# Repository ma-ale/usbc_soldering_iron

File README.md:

# USB-C Soldering Iron

Repo for a cool usb-c soldering iron that uses C245 cartridges and power up to 130W.

Read the [project report](doc/report/README.md) (in italian).

# IDEAS

* USB-C connector on the edge of the PCB like the [alientek T90B](https://youtu.be/Xl0IKpvlF3Y?si=ecKIGLwI0vSPZbJ4&t=7) (clamping plate)
* OLED Screen on a separate PCB, same project with a V-Cut
* More compact tip recess, stabilized by a, aluminium ring, maybe bought at the hardware store
* Single screw disassembly
* 13mm grip dimensions and 18mm otherwise
* 1mm walls in PETG
* Add a ~small~ button to the bootsel line

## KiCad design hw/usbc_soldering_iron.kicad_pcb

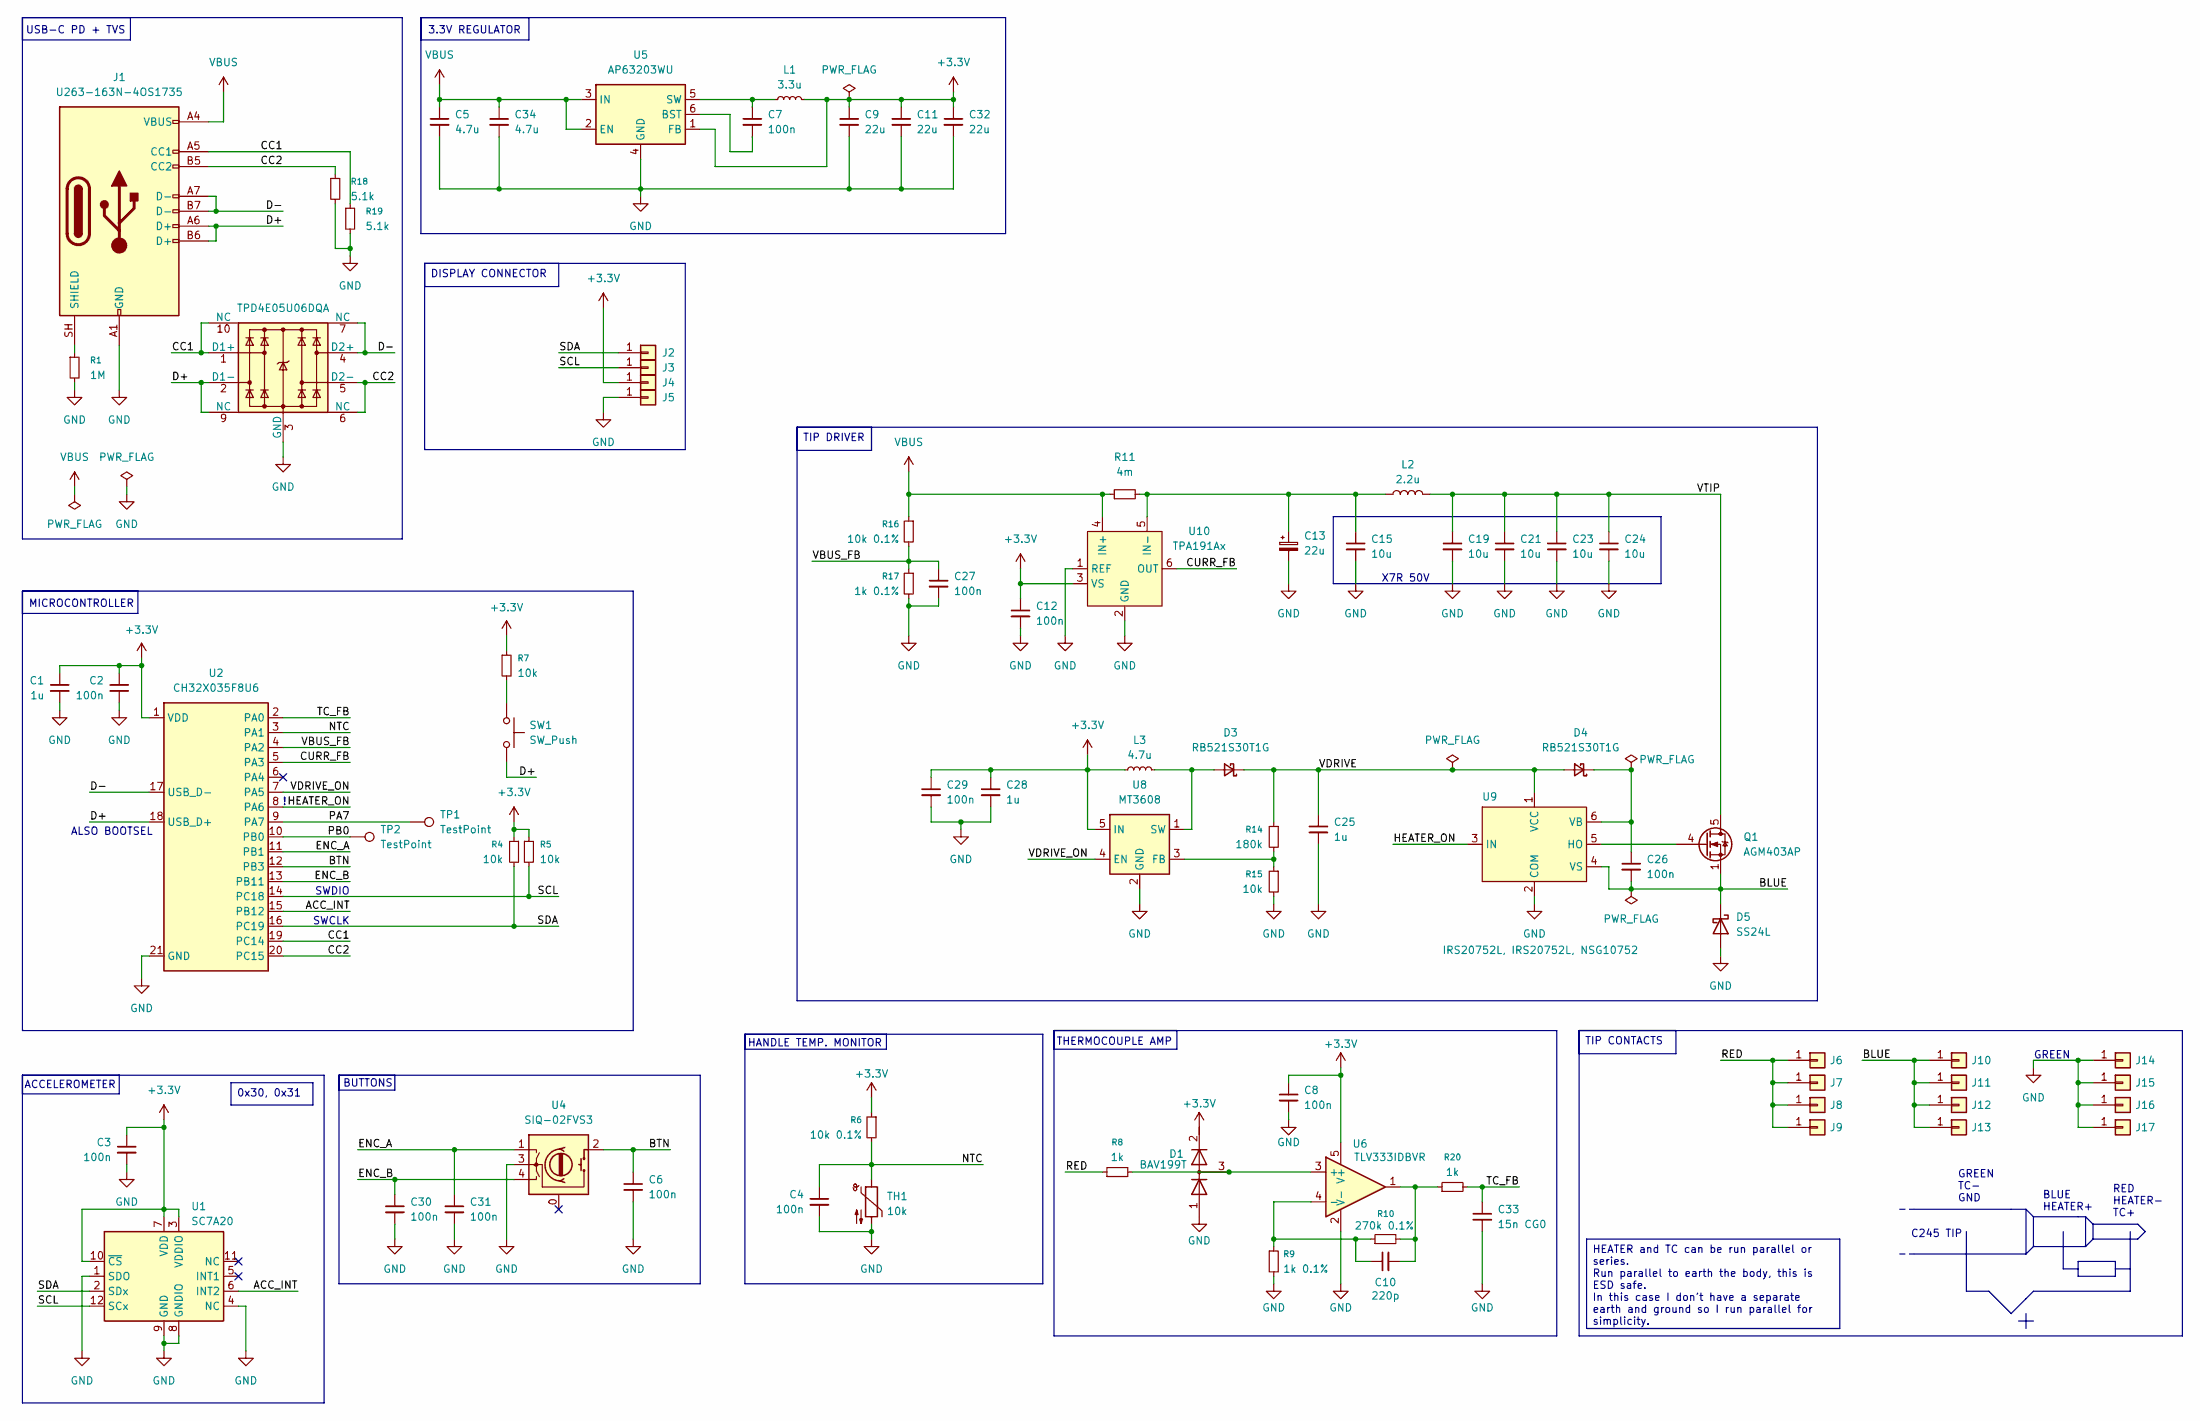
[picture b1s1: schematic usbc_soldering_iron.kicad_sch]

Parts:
C1, C25, C28: 1u; C_0603_1608Metric
C2, C3, C4, C6, C7, C8, C12, C26, C27, C29, C30, C31: 100n; C_0603_1608Metric
C5, C34: 4.7u; C_0805_2012Metric
C9, C11, C32: 22u; C_0603_1608Metric
C10: 220p; C_0603_1608Metric
C13: 22u; CP-SMD_L7.3-W4.3-FD
C15, C19, C21, C23, C24: 10u; C_1210_3225Metric
C33: 15n CG0; C_0603_1608Metric
D1: BAV199T; SOT-523
D3, D4: RB521S30T1G; D_SOD-523
D5: SS24L; D_SOD-123F
J1: U263-163N-4OS1735; USB-SMD_HC-TYPE-C-24P-CP1.0-5A-L10.45-01
J2, J3, J4, J5: Conn_01x01; SolderWirePad_1x01_SMD_1x2mm
J6, J7, J8, J9, J10, J11, J12, J13, J14, J15, J16, J17: Conn_01x01; SolderWire-1sqmm_1x01_D1.4mm_OD2.7mm
L1: 3.3u; L_Changjiang_FTC201612S_Handsolder
L2: 2.2u; L_Changjiang_FNR4030S_Handsolder
L3: 4.7u; L_0603_1608Metric
Q1: AGM403AP; VSON-8_3.3x3.3mm_P0.65mm_NexFET
R1: 1M; R_0603_1608Metric
R4, R5, R7, R15: 10k; R_0603_1608Metric
R6, R16: 10k 0.1%; R_0603_1608Metric
R8, R20: 1k; R_0603_1608Metric
R9, R17: 1k 0.1%; R_0603_1608Metric
R10: 270k 0.1%; R_0603_1608Metric
R11: 4m; R_1206_3216Metric
R14: 180k; R_0603_1608Metric
R18, R19: 5.1k; R_0603_1608Metric
SW1: SW_Push; SW_PUSH_GT-TS201A-H0065
TH1: 10k; R_0603_1608Metric
TP1, TP2: TestPoint; TestPoint_Pad_D1.0mm
U1: SC7A20; LGA-12_2x2mm_P0.5mm
U2: CH32X035F8U6; QFN-20-1EP_3x3mm_P0.4mm_EP1.65x1.65mm; LCSC C42442062
U3: TPD4E05U06DQA; USON-10_2.5x1.0mm_P0.5mm
U4: SIQ-02FVS3; SIQ-02FVS3_Rotary_Encoder
U5: AP63203WU; TSOT-23-6
U6: TLV333IDBVR; SOT-23-5
U8: MT3608; SOT-23-6
U9: IRS20752L, IRS20752L, NSG10752; SOT-23-6
U10: TPA191Ax; SOT-363_SC-70-6

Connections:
+3.3V: C1.1, C2.1, C3.1, C8.1, C9.1, C11.1, C12.1, C28.1, C29.1, C32.1, D1.2 (K), J4.1 (Pin_1_1), L1.2, L3.1, R4.1, R5.1, R6.1, R7.1, U1.3 (VDDIO), U1.7 (VDD), U1.10 (~CS), U2.1 (VDD), U5.1 (FB), U6.5 (V+), U8.5 (IN), U10.3 (VS)
/ACC_INT: U1.6 (INT2), U2.15 (PB12)
/BLUE: C26.2, D5.1 (K), J10.1 (Pin_1_1), J11.1 (Pin_1_1), J12.1 (Pin_1_1), J13.1 (Pin_1_1), Q1.1 (S), Q1.2 (S), Q1.3 (S), U9.4 (VS)
/BTN: C6.1, U2.12 (PB3), U4.2
/CC1: J1.A5 (CC1), R19.1, U2.19 (PC14), U3.1 (D1+), U3.10 (NC)
/CC2: J1.B5 (CC2), R18.1, U2.20 (PC15), U3.5 (D2-), U3.6 (NC)
/CURR_FB: U2.5 (PA3), U10.6 (OUT)
/D+: J1.A6 (D+), J1.B6 (D+), SW1.2, U2.18 (USB_D+), U3.2 (D1-), U3.9 (NC)
/D-: J1.A7 (D-), J1.B7 (D-), U2.17 (USB_D-), U3.4 (D2+), U3.7 (NC)
/ENC_A: C31.1, U2.11 (PB1), U4.1
/ENC_B: C30.1, U2.13 (PB11), U4.4
/HEATER_ON: U2.8 (PA6), U9.3 (IN)
/NTC: C4.1, R6.2, TH1.1, U2.3 (PA1)
/PA7: TP1.1 (1_1), U2.9 (PA7)
/PB0: TP2.1 (1_1), U2.10 (PB0)
/RED: J6.1 (Pin_1_1), J7.1 (Pin_1_1), J8.1 (Pin_1_1), J9.1 (Pin_1_1), R8.1
/SCL: J3.1 (Pin_1_1), R5.2, U1.12 (SCx), U2.14 (PC18)
/SDA: J2.1 (Pin_1_1), R4.2, U1.2 (SDx), U2.16 (PC19)
/TC_FB: C33.1, R20.2, U2.2 (PA0)
/VBUS_FB: C27.1, R16.2, R17.1, U2.4 (PA2)
/VDRIVE: C25.1, D3.1 (K), D4.2 (A), R14.1, U9.1 (VCC)
/VDRIVE_ON: U2.7 (PA5), U8.4 (EN)
/VTIP: C19.1, C21.1, C23.1, C24.1, L2.2, Q1.5 (D)
GND: C1.2, C2.2, C3.2, C4.2, C5.2, C6.2, C8.2, C9.2, C11.2, C12.2, C13.2, C15.2, C19.2, C21.2, C23.2, C24.2, C25.2, C27.2, C28.2, C29.2, C30.2, C31.2, C32.2, C33.2, C34.2, D1.1 (A), D5.2 (A), J1.A1 (GND), J1.A12 (GND), J1.B1 (GND), J1.B12 (GND), J5.1 (Pin_1_1), J14.1 (Pin_1_1), J15.1 (Pin_1_1), J16.1 (Pin_1_1), J17.1 (Pin_1_1), R1.2, R9.2, R15.2, R17.2, R18.2, R19.2, TH1.2, U1.1 (SDO), U1.4 (NC), U1.8 (GNDIO), U1.9 (GND), U2.21 (GND), U3.3 (GND), U3.8 (GND), U4.3, U5.4 (GND), U6.2 (V-), U8.2 (GND), U9.2 (COM), U10.1 (REF), U10.2 (GND)
unnamed: C10.2, R10.2, R20.1, U6.1
unnamed: D1.3 (common), R8.2, U6.3 (+)
unnamed: D3.2 (A), L3.2, U8.1 (SW)
unnamed: C26.1, D4.1 (K), U9.6 (VB)
unnamed: J1.SH (SHIELD), R1.1
unnamed: Q1.4 (G), U9.5 (HO)
unnamed: R7.2, SW1.1
unnamed: C7.2, U5.6 (BST)
unnamed: C7.1, L1.1, U5.5 (SW)
unnamed: C10.1, R9.1, R10.1, U6.4 (-)
unnamed: R14.2, R15.1, U8.3 (FB)
unnamed: C13.1, C15.1, L2.1, R11.2, U10.5 (IN-)
VBUS: C5.1, C34.1, J1.A4 (VBUS), J1.A9 (VBUS), J1.B4 (VBUS), J1.B9 (VBUS), R11.1, R16.1, U5.2 (EN), U5.3 (IN), U10.4 (IN+)

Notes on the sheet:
SWCLK
RED HEATER- TC+
3.3V REGULATOR
SWDIO
ALSO BOOTSEL
USB-C PD + TVS
BUTTONS
ACCELEROMETER
BLUE HEATER+
HANDLE TEMP. MONITOR
GREEN
X7R 50V
THERMOCOUPLE AMP
MICROCONTROLLER
C245 TIP
GREEN TC- GND
TIP DRIVER
0x30, 0x31
DISPLAY CONNECTOR
HEATER and TC can be run parallel or series. Run parallel to earth the body, this is ESD safe. In this case I don't have a separate earth and ground so I run parallel for simplicity.
TIP CONTACTS

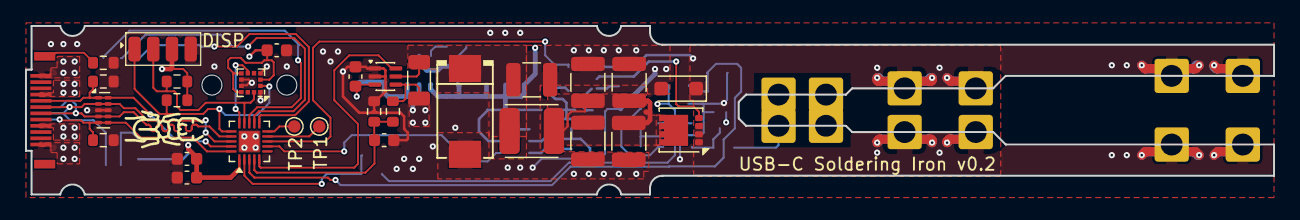
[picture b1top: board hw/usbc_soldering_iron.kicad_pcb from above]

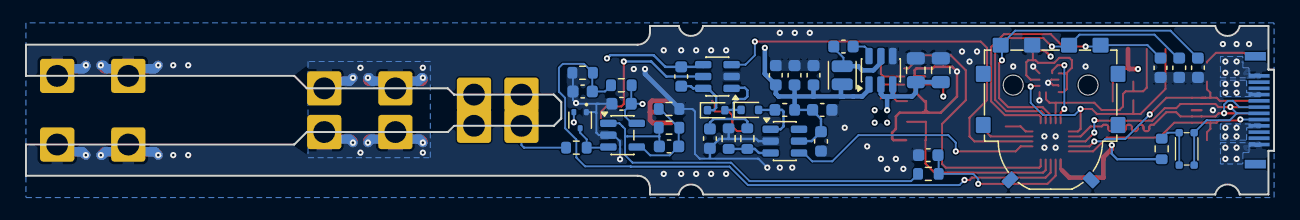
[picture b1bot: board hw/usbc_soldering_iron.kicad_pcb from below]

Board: 4 copper layers, 100.0 x 13.5 mm, 82 parts (37 on the bottom side), 37 nets.

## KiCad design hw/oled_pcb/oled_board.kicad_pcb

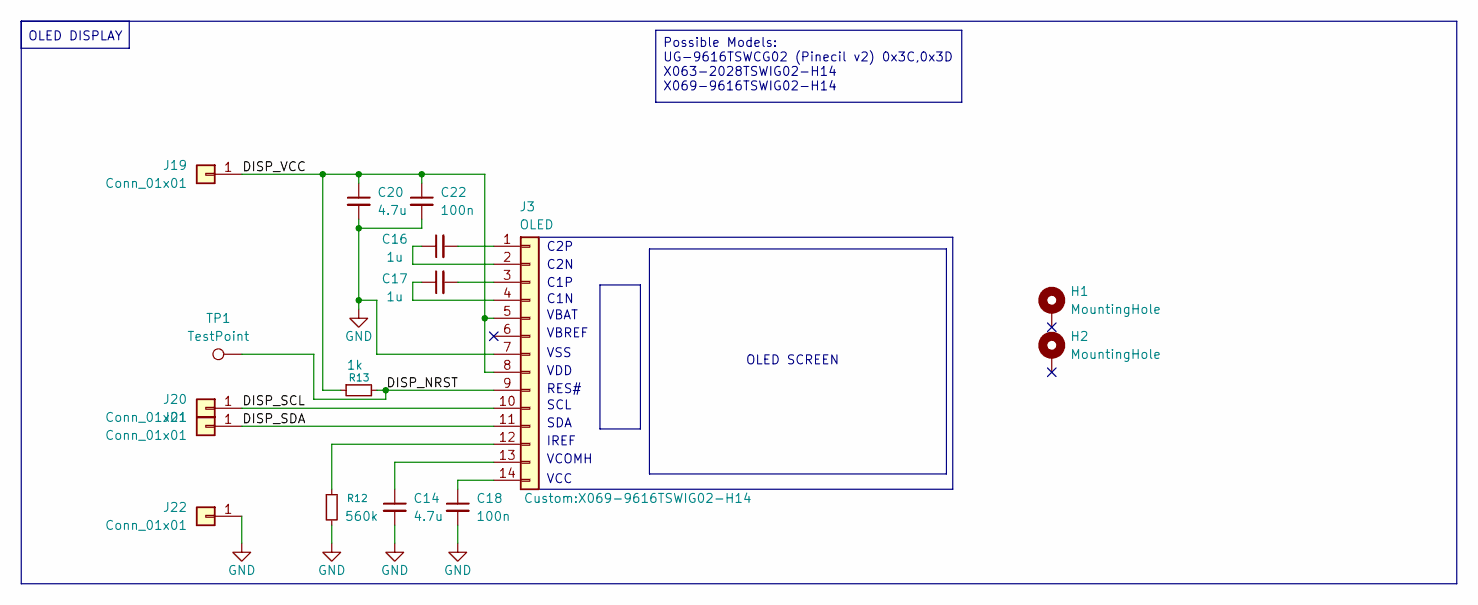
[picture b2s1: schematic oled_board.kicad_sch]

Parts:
C14, C20: 4.7u; C_0603_1608Metric
C16, C17: 1u; C_0603_1608Metric
C18, C22: 100n; C_0603_1608Metric
H1, H2: MountingHole; Mounting_Wuerth_WA-SMSI-M2_H0.5mm_9774005243
J3: OLED; X069-9616TSWIG02-H14
J19, J20, J21, J22: Conn_01x01; SolderWirePad_1x01_SMD_1x2mm
R12: 560k; R_0603_1608Metric
R13: 1k; R_0603_1608Metric
TP1: TestPoint; TestPoint_Pad_D1.0mm

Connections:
/DISP_NRST: J3.9, R13.2, TP1.1 (1_1)
/DISP_SCL: J3.10, J20.1 (Pin_1_1)
/DISP_SDA: J3.11, J21.1 (Pin_1_1)
/DISP_VCC: C20.1, C22.1, J3.5, J3.8, J19.1 (Pin_1_1), R13.1
GND: C14.2, C18.2, C20.2, C22.2, J3.7, J22.1 (Pin_1_1), R12.2
unnamed: C16.2, J3.1
unnamed: C16.1, J3.2
unnamed: C17.2, J3.3
unnamed: C17.1, J3.4
unnamed: J3.12, R12.1
unnamed: C14.1, J3.13
unnamed: C18.1, J3.14

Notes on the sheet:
C2N
SCL
RES#
C1P
IREF
C1N
C2P
VDD
OLED SCREEN
VCC
SDA
VBREF
OLED DISPLAY
VBAT
VSS
VCOMH
Possible Models: UG-9616TSWCG02 (Pinecil v2) 0x3C,0x3D X063-2028TSWIG02-H14 X069-9616TSWIG02-H14

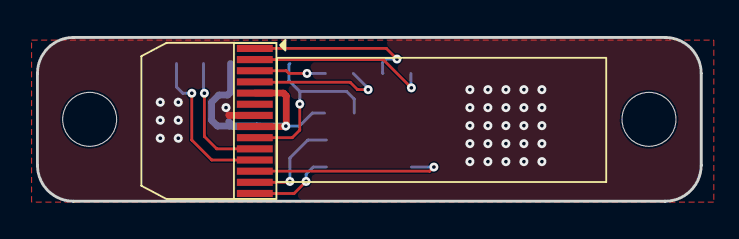
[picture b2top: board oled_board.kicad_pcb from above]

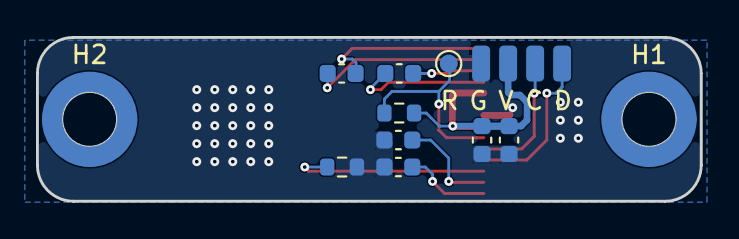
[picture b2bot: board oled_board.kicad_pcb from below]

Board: 2 copper layers, 36.9 x 9.1 mm, 16 parts (15 on the bottom side), 12 nets.

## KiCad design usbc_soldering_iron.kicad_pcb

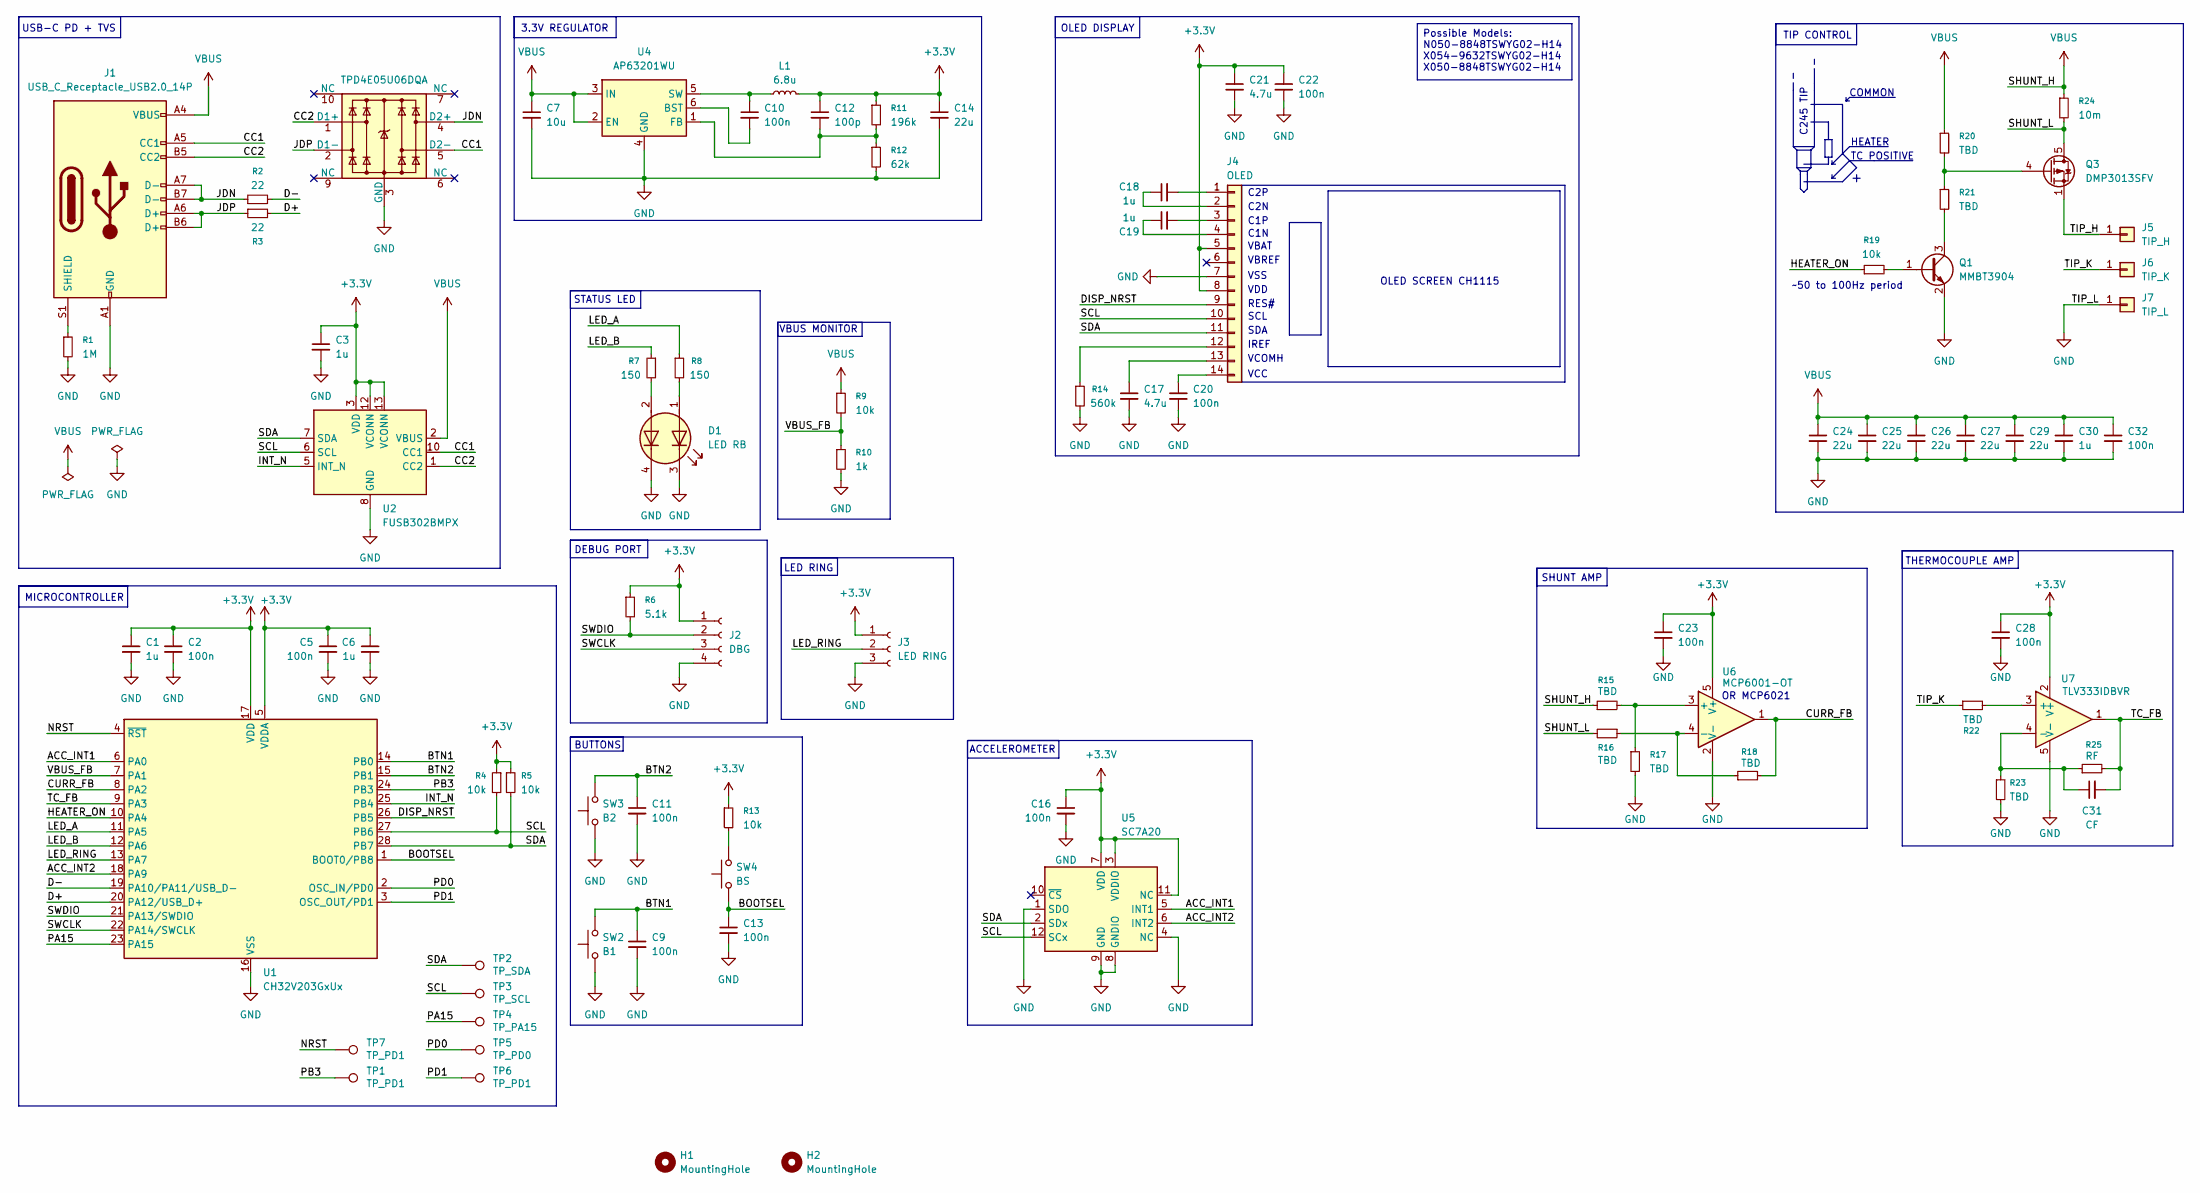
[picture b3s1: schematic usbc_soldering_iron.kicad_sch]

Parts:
C1, C3, C6, C18, C19: 1u; C_0603_1608Metric
C2, C5, C9, C10, C11, C13, C16, C20, C22, C23, C28, C32: 100n; C_0603_1608Metric
C7: 10u; C_0805_2012Metric
C12: 100p; C_0603_1608Metric
C14, C24, C25, C26, C27, C29: 22u; C_0805_2012Metric
C17, C21: 4.7u; C_0603_1608Metric
C30: 1u; C_0805_2012Metric
C31: CF; C_0603_1608Metric
D1: LED RB; LED_Avago_PLCC4_3.2x2.8mm_CW
H1, H2: MountingHole; MountingHole_2.2mm_M2
J1: USB_C_Receptacle_USB2.0_14P; USB_C_Receptacle_G-Switch_GT-USB-7025
J2: DBG
J3: LED RING
J4: OLED; FPC_14
J5: TIP_H
J6: TIP_K
J7: TIP_L
L1: 6.8u; L_Changjiang_FTC201607S
Q1: MMBT3904; SOT-23
Q3: DMP3013SFV; Diodes_PowerDI3333-8
R1: 1M; R_0603_1608Metric
R2, R3: 22; R_0603_1608Metric
R4, R5, R9, R13, R19: 10k; R_0603_1608Metric
R6: 5.1k; R_0603_1608Metric
R7, R8: 150; R_0603_1608Metric
R10: 1k; R_0603_1608Metric
R11: 196k; R_0603_1608Metric
R12: 62k; R_0603_1608Metric
R14: 560k; R_0603_1608Metric
R15, R16, R17, R18, R20, R21, R22, R23: TBD; R_0603_1608Metric
R24: 10m; R_1206_3216Metric
R25: RF; R_0603_1608Metric
SW2: B1; SW_SPST_TS-1088-xR020
SW3: B2; SW_SPST_TS-1088-xR020
SW4: BS; SW_SPST_TS-1088-xR020
TP1, TP6, TP7: TP_PD1; TestPoint_Pad_D1.0mm
TP2: TP_SDA; TestPoint_Pad_D1.0mm
TP3: TP_SCL; TestPoint_Pad_D1.0mm
TP4: TP_PA15; TestPoint_Pad_D1.0mm
TP5: TP_PD0; TestPoint_Pad_D1.0mm
U1: CH32V203GxUx; WQFN-28-1EP_4x4mm_P0.4mm_EP2.7x2.7mm
U2: FUSB302BMPX; WQFN-14-1EP_2.5x2.5mm_P0.5mm_EP1.45x1.45mm
U4: AP63201WU; TSOT-23-6
U5: SC7A20; LGA-12_2x2mm_P0.5mm
U6: MCP6001-OT; SOT-23-5
U7: TLV333IDBVR; SOT-23-5
U8: TPD4E05U06DQA; USON-10_2.5x1.0mm_P0.5mm

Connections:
+3.3V: C1.1, C2.1, C3.1, C5.1, C6.1, C12.1, C14.1, C16.1, C21.1, C22.1, C23.1, C28.1, J2.1, J3.1, J4.5, J4.8, L1.2, R4.1, R5.1, R6.1, R11.1, R13.1, U1.5 (VDDA), U1.17 (VDD), U2.3 (VDD), U2.4 (VDD), U2.12 (VCONN), U2.13 (VCONN), U5.3 (VDDIO), U5.7 (VDD), U5.11 (NC), U6.5 (V+), U7.2 (V+)
/ACC_INT1: U1.6 (PA0), U5.5 (INT1)
/ACC_INT2: U1.18 (PA9), U5.6 (INT2)
/BOOTSEL: C13.1, SW4.1, U1.1 (BOOT0/PB8)
/BTN1: C9.1, SW2.2, U1.14 (PB0)
/BTN2: C11.1, SW3.2, U1.15 (PB1)
/CC1: J1.A5 (CC1), U2.10 (CC1), U2.11 (CC1), U8.5 (D2-)
/CC2: J1.B5 (CC2), U2.1 (CC2), U2.14 (CC2), U8.1 (D1+)
/CURR_FB: R18.2, U1.8 (PA2), U6.1
/D+: R3.2, U1.20 (PA12/USB_D+)
/D-: R2.2, U1.19 (PA10/PA11/USB_D-)
/DISP_NRST: J4.9, U1.26 (PB5)
/HEATER_ON: R19.1, U1.10 (PA4)
/INT_N: U1.25 (PB4), U2.5 (INT_N)
/JDN: J1.A7 (D-), J1.B7 (D-), R2.1, U8.4 (D2+)
/JDP: J1.A6 (D+), J1.B6 (D+), R3.1, U8.2 (D1-)
/LED_A: R8.1, U1.11 (PA5)
/LED_B: R7.1, U1.12 (PA6)
/LED_RING: J3.2, U1.13 (PA7)
/NRST: TP7.1, U1.4 (~RST)
/PA15: TP4.1, U1.23 (PA15)
/PB3: TP1.1, U1.24 (PB3)
/PD0: TP5.1, U1.2 (OSC_IN/PD0)
/PD1: TP6.1, U1.3 (OSC_OUT/PD1)
/SCL: J4.10, R4.2, TP3.1, U1.27 (PB6), U2.6 (SCL), U5.12 (SCx)
/SDA: J4.11, R5.2, TP2.1, U1.28 (PB7), U2.7 (SDA), U5.2 (SDx)
/SHUNT_L: Q3.5 (D), R16.2, R24.2
/SWCLK: J2.3, U1.22 (PA14/SWCLK)
/SWDIO: J2.2, R6.2, U1.21 (PA13/SWDIO)
/TC_FB: C31.2, R25.2, U1.9 (PA3), U7.1
/TIP_H: J5.1, Q3.1 (S), Q3.2 (S), Q3.3 (S)
/TIP_K: J6.1, R22.1
/VBUS_FB: R9.2, R10.1, U1.7 (PA1)
GND: C1.2, C2.2, C3.2, C5.2, C6.2, C7.2, C9.2, C11.2, C13.2, C14.2, C16.2, C17.2, C20.2, C21.2, C22.2, C23.2, C24.2, C25.2, C26.2, C27.2, C28.2, C29.2, C30.2, C32.2, D1.3 (K1), D1.4 (K2), J1.A1 (GND), J1.A12 (GND), J1.B1 (GND), J1.B12 (GND), J2.4, J3.3, J4.7, J7.1, Q1.2 (E), R1.2, R10.2, R12.2, R14.2, R17.2, R23.2, SW2.1, SW3.1, U1.16 (VSS), U1.29 (VSS), U2.8 (GND), U2.9 (GND), U2.15 (GND), U4.4 (GND), U5.1 (SDO), U5.4 (NC), U5.8 (GNDIO), U5.9 (GND), U6.2 (V-), U7.5 (V-), U8.3 (GND), U8.8 (GND)
unnamed: D1.1 (A1), R8.2
unnamed: D1.2 (A2), R7.2
unnamed: J1.S1 (SHIELD), R1.1
unnamed: C18.2, J4.1
unnamed: C18.1, J4.2
unnamed: C19.2, J4.3
unnamed: C19.1, J4.4
unnamed: J4.12, R14.1
unnamed: C17.1, J4.13
unnamed: C20.1, J4.14
unnamed: Q1.1 (B), R19.2
unnamed: Q1.3 (C), R21.2
unnamed: Q3.4 (G), R20.2, R21.1
unnamed: R13.2, SW4.2
unnamed: C10.2, U4.6 (BST)
unnamed: C12.2, R11.2, R12.1, U4.1 (FB)
unnamed: C10.1, L1.1, U4.5 (SW)
unnamed: R15.2, R17.1, U6.3 (+)
unnamed: R16.1, R18.1, U6.4 (-)
unnamed: R22.2, U7.3 (+)
unnamed: C31.1, R23.1, R25.1, U7.4 (-)
VBUS: C7.1, C24.1, C25.1, C26.1, C27.1, C29.1, C30.1, C32.1, J1.A4 (VBUS), J1.A9 (VBUS), J1.B4 (VBUS), J1.B9 (VBUS), R9.1, R15.1, R20.1, R24.1, U2.2 (VBUS), U4.2 (EN), U4.3 (IN)

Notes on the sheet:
COMMON
~50 to 100Hz period
3.3V REGULATOR
C2N
OR MCP6021
USB-C PD + TVS
BUTTONS
DEBUG PORT
SCL
RES#
C1P
ACCELEROMETER
HEATER
IREF
C1N
C2P
VDD
TC POSITIVE
OLED SCREEN CH1115
VCC
TIP CONTROL
SDA
VBREF
SHUNT AMP
STATUS LED
OLED DISPLAY
VBAT
VSS
VCOMH
THERMOCOUPLE AMP
C245 TIP
LED RING
MICROCONTROLLER
VBUS MONITOR
Possible Models: N050-8848TSWYG02-H14 X054-9632TSWYG02-H14 X050-8848TSWYG02-H14

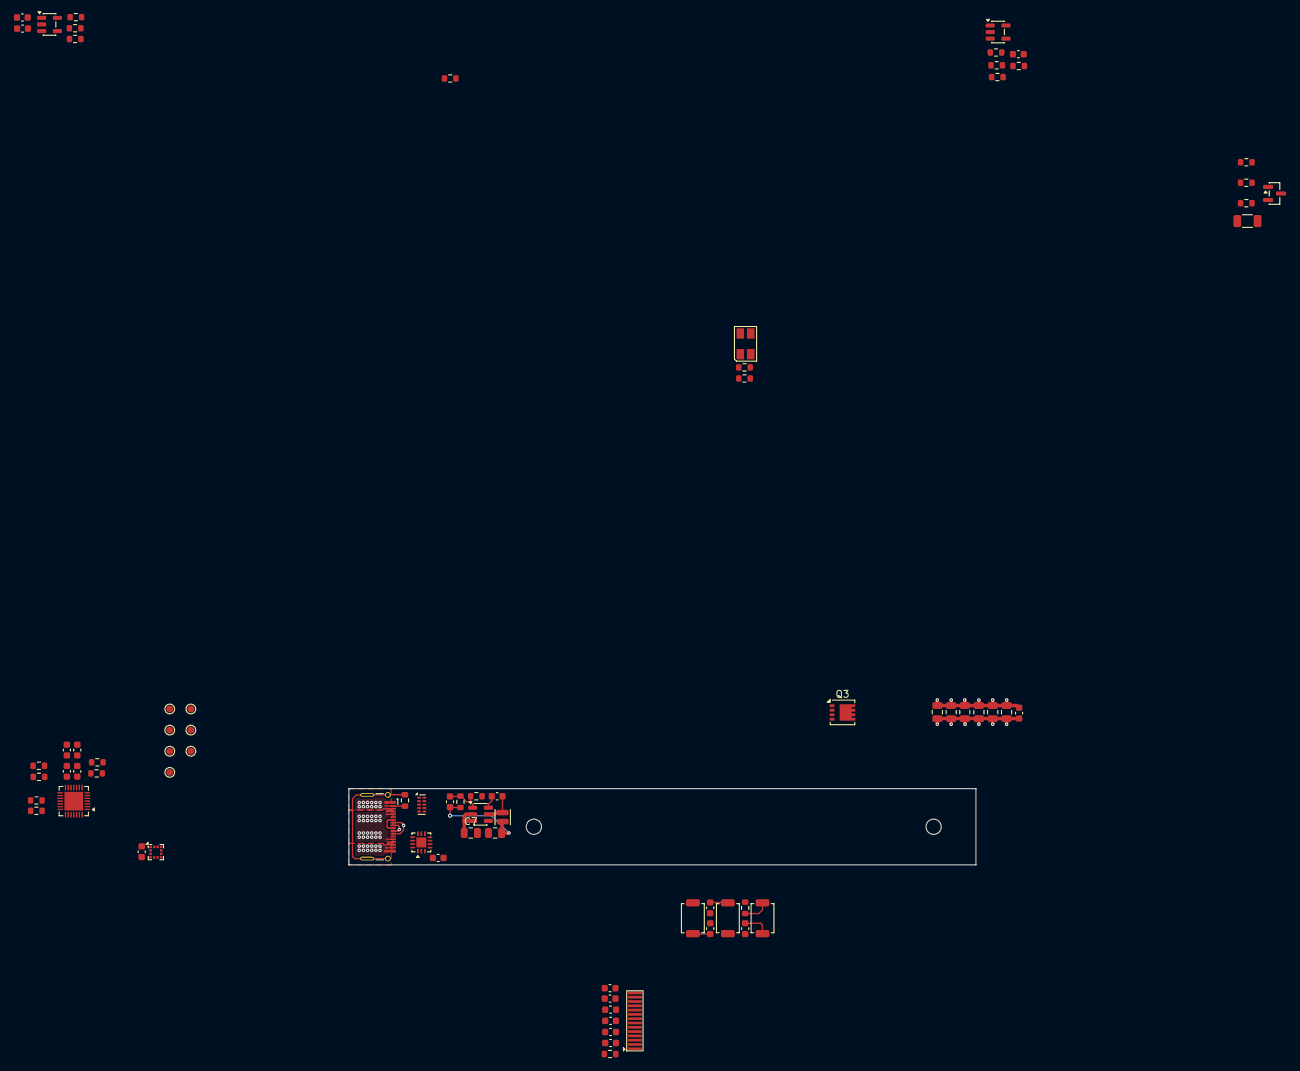
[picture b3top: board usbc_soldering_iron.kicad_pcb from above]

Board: 4 copper layers, 90.5 x 11.0 mm, 79 parts (0 on the bottom side), 53 nets.

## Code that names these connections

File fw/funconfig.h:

#ifndef _FUNCONFIG_H
#define _FUNCONFIG_H

#define FUNCONF_USE_DEBUGPRINTF 0 // can only have one printf
#define FUNCONF_USE_USBPRINTF   1
#define FUNCONF_DEBUG_HARDFAULT 0
#define CH32X035                1
#define I2C_TARGET              I2C1
#define FRAME_TIME_MS           20 // 50Hz
#define PWM_FREQ_HZ             100000 // TIM3 PWM frequency

// Pin definitions
#define PIN_VBUS     PA0  // vbus voltage feedback
#define PIN_CURRENT  PA1  // current feedback
#define PIN_NTC      PA2  // ntc temperature sensor
#define PIN_TEMP     PA3  // thermocouple amplifier
#define PIN_12V      PA5  // 12V regulator enable
#define PIN_HEATER   PA6  // power mosfet gate control
#define PIN_ENC_A    PB3  // rotary encoder A
#define PIN_ENC_B    PB11 // rotary encoder B
#define PIN_BTN      PB1  // rotary encoder button

// Analog channel definitions
#define VBUS_ADC_CHANNEL    ANALOG_0 // PA0
#define CURRENT_ADC_CHANNEL ANALOG_1 // PA1
#define NTC_ADC_CHANNEL     ANALOG_2 // PA2
#define TEMP_ADC_CHANNEL    ANALOG_3 // PA3
#define VREF_INT_CHANNEL    15       // Internal channel set to 1.2V reference

#define ENCODER_INV true
#define ENCODER_FAST 3

#define MAX_BOARD_TEMP 50
#define MAX_TIP_TEMP   500
#define TURN_OFF_DELAY 3
#define CYCLES_PER_MEASURE 2
#define BOARD_MAX_VOLTAGE 28000
#define MIN_TIP_SET_TEMP 100
#define MAX_TIP_SET_TEMP 420



#endif // _FUNCONFIG_H

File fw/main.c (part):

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	btn->now = state;
}

#define button_rising(btn) ((btn).now == true && (btn).prev == false)
#define button_falling(btn) ((btn).now == false && (btn).prev == true)


/* ------------------------------ Global State ------------------------------ */
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
	// FIXME: even with interrupts disabled and debounce, a single detent triggers
	// multiple interrupts, leading to multiple encoder updates in a short time.
	if (funDigitalRead(PIN_BTN) == 0) return;
	bool a = funDigitalRead(PIN_ENC_A);
	bool b = funDigitalRead(PIN_ENC_B);
	Delay_Us(100);
	if (a != funDigitalRead(PIN_ENC_A) || b != funDigitalRead(PIN_ENC_B))
		return; // debounce

	uint8_t current_state = (a << 1) | b;
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	last_state = current_state;
}

// Attached to PIN_ENC_A rising and falling edges
void EXTI7_0_IRQHandler(void) __attribute__((interrupt));
void EXTI7_0_IRQHandler(void)
{
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	__enable_irq();
}

// Attached to PIN_ENC_B rising and falling edges
void EXTI15_8_IRQHandler(void) __attribute__((interrupt));
void EXTI15_8_IRQHandler(void)
{
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	AFIO->PCFR1 &= ~(0b0111 << 24);
	AFIO->PCFR1 |=   0b0100 << 24;

	// Map SCL to PC18 and SDA to PC19
	AFIO->PCFR1 |= 0b0101 << 2;
	// Manually set the I2C pins to Alternate Function IO,  CNF=10b, MODE=10b
	GPIOC->CFGXR &= ~((0xF << 8) | (0xF << 12)); // first clear the bits
	// then set them
	GPIOC->CFGXR |= 0b1010 << 8; // PC18
	GPIOC->CFGXR |= 0b1010 << 12; // PC19
}


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	// (= initiate update) (auto-clears)
	TIM3->CHCTLR1 |= TIM_OC1M_2 | TIM_OC1M_1 | TIM_OC1PE;

	// Enable channel 1 output (PA6)
	TIM3->CCER |= TIM_CC1E | ( TIM_CC1P & TIM3_DEFAULT );

	// CTLR1: default is up, events generated, edge align
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	// ====================== Analog pin configuration ====================== //
	funPinMode(PIN_VBUS, GPIO_CFGLR_IN_ANALOG);
	funPinMode(PIN_CURRENT, GPIO_CFGLR_IN_ANALOG);
	funPinMode(PIN_NTC, GPIO_CFGLR_IN_ANALOG);
	funPinMode(PIN_TEMP, GPIO_CFGLR_IN_ANALOG);

	// Analog inputs setup (dma and injection conversion)
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	funPinMode(PIN_DISP_RST, GPIO_CFGLR_OUT_10Mhz_PP);
	funDigitalWrite(PIN_DISP_RST, 1);

	funPinMode(PIN_ENC_A, GPIO_CFGLR_IN_PUPD); // enable pull-up/down
	funDigitalWrite(PIN_ENC_A, 1);             // specify pull-up
	funPinMode(PIN_ENC_B, GPIO_CFGLR_IN_PUPD); // enable pull-up/down
	funDigitalWrite(PIN_ENC_B, 1);             // specify pull-up
	funPinMode(PIN_BTN, GPIO_CFGLR_IN_FLOAT);

	// Setup PWM timer, includes pin setup
	setup_pwm();
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
	// =========================== Encoder Setup ============================ //
	// Configure the IO as an interrupt.
	// PIN_ENC_B is on port B, channel 11
	AFIO->EXTICR1 |= AFIO_EXTICR1_EXTI11_PB; // Port B channel (pin) 11
	EXTI->INTENR |= EXTI_INTENR_MR11;        // Enable EXT11
	EXTI->FTENR |= EXTI_FTENR_TR11;          // Falling edge trigger
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	// enable interrupt
	NVIC_EnableIRQ(EXTI15_8_IRQn);

	// PIN_ENC_A is on port B, channel 3
	AFIO->EXTICR1 |= AFIO_EXTICR1_EXTI3_PB; // Port B channel (pin) 3
	EXTI->INTENR |= EXTI_INTENR_MR3;        // Enable EXT3
	EXTI->FTENR |= EXTI_FTENR_TR3;          // Falling edge trigger
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static inline void update_tip_and_vcc(void)
{
	// Tip calibration factors
	const fp16_t tip_k = num2fp(0, 14473, 5);
	const fp16_t tip_off = num2fp(0, 0, 0);

	adc_injection_conversion();
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	struct button btn;
	button_init(&btn, true);
	for (;;) {
		button_update(&btn, funDigitalRead(PIN_BTN));

		update_power_and_temperature();

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
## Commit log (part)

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2026-01-16 board dimensions and different components
2026-01-16 some things needed to be 0805
2026-01-20 progress on schematic and ui draft
2026-01-20 mosfet protection and low side current sensing
2026-01-20 removed LED and added NTC
2026-01-22 added tip 3d model
2026-01-22 ui font concept update
2026-01-22 update model to freecad stable version
2026-01-22 added pads for tip connector
2026-01-24 big update
    * drawn contacts
    * done board outline in cad
    * reverted to high-side monitoring with ad-hoc ic
2026-01-24 FIX MOSFET ORIENTATION
2026-02-03 excel dei buck
2026-02-03 stima della massima potenza dissipata
2026-02-07 buck converter
2026-02-07 ltspice simulations
2026-02-10 stuff
2026-02-13 mosfets and driver
2026-02-14 more realistic pi filter
2026-02-14 different mosfets
2026-02-17 complete model test
2026-02-18 work on model
2026-02-18 rotary encoder and model for usb receptacle
2026-02-18 started work on report
2026-02-19 smile for the camera
2026-02-19 changed power stage and monitoring ICs
2026-02-19 added README
2026-02-19 more work on report
2026-02-20 simulate the gate driver IC
2026-02-20 report: work on mosfet and driver
2026-02-22 separate boost for gate driver
2026-02-22 removed i2c temp sensor and high side bus switch
2026-02-22 preliminary BOM and schematic
2026-02-22 fixed buck, same family
2026-02-24 revised schematic
    - changed mcu to ch32x035
    - removed fusbxx pd controller, since it's integrated into the mcu
    - reverted the ina226 to the tpa191
    - removed temperature sensor in favor of an ntc
    - routed tip contacts correctly
2026-02-24 bom for revised schematic
2026-02-24 changed usb-c connector
2026-02-25 simulazioni con derating per dc bias
2026-02-25 link sul derating
2026-02-25 flyback diode to the tip
2026-02-25 list of good mosfets
2026-02-26 removed the diocane filter in favor of capacitors
2026-02-28 different capacitors in sim with pi filter
2026-02-28 trying new capacitors
2026-02-28 samsung mlccs
2026-02-28 Revert "samsung mlccs"
    This reverts commit f0811c47dd4636ecc8ad168b69960cac51ca3142.
2026-02-28 Revert "trying new capacitors"
    This reverts commit 6cb91291f39b019d0baab4303cfee70c88c38332.
2026-02-28 Revert "different capacitors in sim with pi filter"
    This reverts commit 30c0aa5cba112ce18ca016d04ddbcca1eab52d60.
2026-02-28 different smaller capacitor
2026-02-28 different capacitors and new bom
2026-03-01 ceramic capacitor
2026-03-02 new filter design, may work lmao
2026-03-05 some component changes
2026-03-06 boxed version
2026-03-07 test pads
2026-03-08 finished pcb
2026-03-09 switch-off simulations and in-stock capacitors
2026-03-10 silkscreen
2026-03-10 different current sensor
2026-03-11 minor tweaks
2026-03-11 lcsc order bom
2026-03-21 3D model of first enclosure
2026-03-25 firmware setup
2026-03-25 test new outline
2026-03-25 some todos
2026-03-25 updated to kicad 10.0
2026-04-04 first (non working) programmer
2026-04-04 better ignore
2026-04-04 technical manuals of the mcu
2026-04-05 refined implementation
2026-04-05 independent programmer
2026-04-05 project start
2026-04-09 firmware not working
2026-04-09 it talks
2026-04-09 read some adcs
2026-04-10 more work on basic functions
2026-04-11 interrupt-based encoder
2026-04-16 i2c test and display
2026-04-17 try to set higher contrast
2026-04-17 push script to generate NTC lut
2026-04-18 moved i2c setup to it's own function
2026-04-18 scan correct I2C bus
2026-04-19 Refactor ADC reading and conversion
    Introduce `VCC_MV` to `funconfig.h` for consistent voltage readings.
    Add `get_current_ma` function to `main.c` for clearer current
    calculations.
    Remove unused `PIN_LED` and `Delay_Ms(5000)` from `main.c`.
    Update VBUS voltage calculation to use `VCC_MV`.
    Print TIP sensor voltage in millivolts instead of raw ADC values.
2026-04-19 draw useful info on screen
2026-04-19 added fixed point exponential average filters
2026-04-19 use ssd1312 display (soldered)
2026-04-19 indentation to tabs
2026-04-19 correct use of #if defined check
2026-04-21 ADC conversion and DMA
    Setup ADC conversions to happen automatically, transferring results to a buffer
    using DMA, also set up channel injection, where instead the tip temperature is
    read sinchronously
2026-04-21 i2c at 400kHz
2026-04-21 removed unused command
2026-04-21 started work on PD negotiation
2026-04-22 print highest voltage and select 9v with button
2026-04-23 parallel compilation with redefined make rules
2026-04-23 removed allucinated functions
2026-04-23 const qualifier for sendBytes
2026-04-24 Add SC7A20 accelerometer support
    !!! AI GENERATED MESSAGE !!!
    This commit introduces support for the SC7A20 accelerometer.
    The accelerometer readings can now be displayed on the screen,
    and the display mode can be toggled using the encoder.
    Additionally, the EMA filter constants for voltage and current
    readings have been updated from K2 to K4 for potentially smoother
2026-04-25 comment on adc conversion
2026-04-26 pwm generation and tip driving
2026-04-28 changed _k to _c to reflect reality, tip temperature approx
2026-04-28 removed usb commands
2026-04-30 first temperature controller
2026-04-30 moved defines to funconfig.h
2026-05-01 moved pd negotiation to owm module
2026-05-01 reverted pwm frequency to 100khz
    Also recompile on header change
2026-05-01 reduced i2c timeout
2026-05-01 fix logic errors
2026-05-03 state machine encoder logic and first simple menu
2026-05-05 start work on EPR support
2026-05-08 start work on PID controller
2026-05-08 TODOs for usbpd EPR impl
2026-05-10 fix delta calc to signed
2026-05-10 use FR_math for fixed point arithmetic
2026-05-10 fix FR_math impl
2026-05-11 fix encoder
2026-05-11 different PID
2026-05-11 PID calibration
2026-05-12 shrim
2026-05-12 avoid string parsing
2026-05-12 new graphics
2026-05-13 different PID controller
2026-05-14 hand rolled fixed point math
2026-05-15 remove negative windup
2026-05-15 encoder "fast lane"
2026-05-15 draw degrees C or F
2026-05-15 moved isqrt to filter.h
2026-05-15 moved ui stuff
2026-05-16 one comment on encoder
2026-05-16 moved setup to it's own function
2026-05-16 some comments and attribution
2026-05-16 oops, actually call setup()
2026-05-16 tweak pid for less overshoot
2026-05-16 100W
2026-05-18 removed programmer
2026-05-18 included protothreads library
2026-05-18 tweaked shrim
2026-05-18 better readme
2026-05-22 use bigger display
2026-05-22 better default temp
2026-05-24 changed inductor footprint to correct one
2026-05-24 input capacitors near boost
2026-05-24 ref of tpa191 to gnd
2026-05-24 corrected tlv333 pin assignment
2026-05-24 5.1k resistors in cc1/2
2026-05-25 debounce caps on encoder and silkscreen adj
2026-05-26 removed diode in programming header
2026-05-26 more capacitors in main buck
2026-05-26 better protection diode for tlv333
2026-05-27 new footprint for big inductor
2026-05-27 swapped protothreads library with custom coroutines library
2026-05-29 VCC calibration with internal reference
2026-05-29 static check for feature compat in coroutine.h
2026-05-29 filter vcc calibration value
2026-05-29 lower tolerance in ntc pullup
2026-05-29 note in LUT comment
2026-05-29 draw some debug info on no pd
2026-05-30 different inductor
2026-05-31 cleanup main pt1
2026-05-31 comments and formatting
2026-05-31 moved state to global
2026-05-31 moved state update to own functions and timer
2026-06-01 suppress unused warnings with coro_end()
2026-06-01 simplified main loop with coroutines
2026-06-02 resistor tollerances
2026-06-02 started work on integrated pcb
2026-06-03 board shape
2026-06-11 new PCB
2026-06-11 edgecuts
2026-06-11 3d filez
2026-06-11 display
2026-06-11 tlv333 rc filter
2026-06-12 vias around tip contacts
2026-06-14 moved models to appropriate directory
2026-06-14 oled board
2026-06-14 removed oled from main board
2026-06-16 3d files and oled board
2026-06-20 heatshield
2026-06-20 tv333 filter and BOM
2026-06-20 prettier schematic
2026-06-23 enlarged for new heatsink
2026-06-23 minor touch-ups on PCB
2026-06-26 silkscreen and better contacts
2026-06-26 new outline and shell
2026-06-26 jlc export toolkit options
2026-06-27 improved routing
2026-06-27 tighter fit on back side of board
2026-06-28 BOM tweaks and distilled for order
2026-06-30 programming hole on bottom
